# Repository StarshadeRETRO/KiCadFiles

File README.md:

# KiCadFiles
This is a repository of KiCad files for various retro gaming systems and related accessories. Unless otherwise noted, all files in this repository are licensed under the BSD-3-Clause license.

When selling physical products based on the files within this repository, attribution via a text link within the product's listing that leads to this repository as well as a text-based notice indicating the URL of this project and what was used in any included documentation or manuals is considered sufficient for fulfilling the license. If you intend to sell the PCBs be sure to remove the Starshade logo first -- see the section on the logo below for more details. Attribution should not be made in a way that suggests affiliation, endorsement, etc.

## Symbols & Footprints
Symbols and footprints in this repository are used in our other projects. You can use them in your projects too!

## PCBs
This repository contains a mix of finished, working, and work-in-progress PCBs as well as PCBs that are not intended to be used as-is but rather as templates you can use to start a project with accurate dimensions that will fit into the OEM location.

## The Starshade Logo
The Starshade logo is used many times throughout this repository, however, it is ***not*** included as part of the project's open license. You *may **not*** use the logo outside of this repository without permission. You **must** remove the logo from products you produce for commercial purposes (i.e. resale, promotion, etc). The logo can be left as is when having PCBs produced for personal use (limit of 5 PCBs per type/revision).

Other than not being able to use Starshade logo there are no further restrictions on commercial use. After removing the logo there are no limits on use, production run size, etc. Removal of the logo is primarily to avoid confusion about who produced/provided the PCB.

## Donations
All donations made to the project go towards furthering this and other projects. They are used to purchase equipment, components, etc. If you want your donation to go towards something specific, you can contact us before making it so we can ensure that it happens. We can provide proof that your donation went towards your desired goal if it is possible/practical.

## Store
Profit from purchases made from the [StarshadeRETRO store](https://store.starshade.dev/) goes towards furthering the development of various projects, including this one, the same as donations do. The only difference is you get something in return when you buy from the store. This is generally preferred over a direct contribution so that you get something in return.

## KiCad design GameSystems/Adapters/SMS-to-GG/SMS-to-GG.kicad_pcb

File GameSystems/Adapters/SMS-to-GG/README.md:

# SMS-to-GG Adapter
Converts a Master System slot to Game Gear for dumping cartridges. Intended for use with the [OSCR HW5](https://github.com/sanni/cartreader).

If getting this made, use a 1.6mm or 1.4mm PCB thickness. 1.6mm is a little tight but is recommended. It keeps the adapter more stable when inserting and removing GG cartridges. 1.4mm will fit a little easier but will wobble a bit when inserting and removing cartridges. While most SMS games seem to be 1.55mm, some SMS games are 1.7mm, so while 1.6mm is a bit tight it's not unrealistic for the system.

You can purchase this adapter [from our store](https://store.starshade.dev/en-gb/product/oscr-and-accessories/oscr-accessories/oscr-adapter-game-gear).

## Revision History
| Rev | Description                                                                                   | Status          |
| --- | --------------------------------------------------------------------------------------------- | --------------- |
| 1   | Initial                                                                                       | ❌ Broken       |
| 2   | Fixed misaligned mounting holes.                                                              | ❌ Incompatible |
| 3   | Moved slot footprint up to allow room for RetroSix GameSlot GG PCB and added a header for it. | ✔️ Verified     |
| 4   | Updated silkscreen and disclaimer formatting and wording. No mechanical difference vs Rev 3.  | ✔️ Verified     |

*SEGA and Game Gear are registered trademarks of SEGA CORPORATION (Japan). SEGA Master System is a trademark of Sega of America, Inc./SEGA CORPORATION (Japan). Neither affiliated with, nor authorized, sponsored, or approved by SEGA.*
*RetroSix is a registered trademark of Luke Malpass (UK). Neither affiliated with, nor authorized, sponsored, or approved by RetroSix/Luke Malpass.*

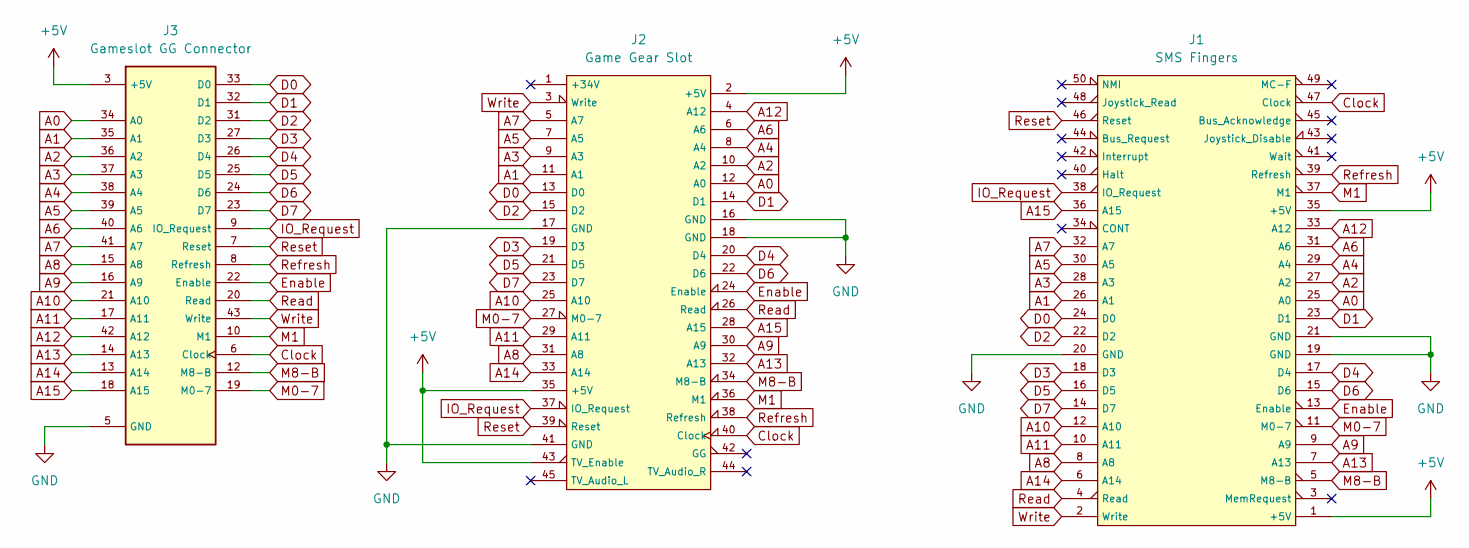
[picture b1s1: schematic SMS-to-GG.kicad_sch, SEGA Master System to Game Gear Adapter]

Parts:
J1: SMS Fingers; SG_SMS_CARTRIDGE_FINGERS
J2: Game Gear Slot; SG_GG_CARTRIDGE_SLOT_2H
J3: Gameslot GG Connector; FPC Connector - 45-pin - Multiple; LCSC C2998867

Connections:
+5V: J1.1 (+5V), J1.35 (+5V), J2.2 (+5V), J2.35 (+5V), J2.43 (TV_Enable), J3.3 (+5V), J3.11 (+5V), J3.44 (+5V)
A0: J1.25 (A0), J2.12 (A0), J3.34 (A0)
A1: J1.26 (A1), J2.11 (A1), J3.35 (A1)
A2: J1.27 (A2), J2.10 (A2), J3.36 (A2)
A3: J1.28 (A3), J2.9 (A3), J3.37 (A3)
A4: J1.29 (A4), J2.8 (A4), J3.38 (A4)
A5: J1.30 (A5), J2.7 (A5), J3.39 (A5)
A6: J1.31 (A6), J2.6 (A6), J3.40 (A6)
A7: J1.32 (A7), J2.5 (A7), J3.41 (A7)
A8: J1.8 (A8), J2.31 (A8), J3.15 (A8)
A9: J1.9 (A9), J2.30 (A9), J3.16 (A9)
A10: J1.12 (A10), J2.25 (A10), J3.21 (A10)
A11: J1.10 (A11), J2.29 (A11), J3.17 (A11)
A12: J1.33 (A12), J2.4 (A12), J3.42 (A12)
A13: J1.7 (A13), J2.32 (A13), J3.14 (A13)
A14: J1.6 (A14), J2.33 (A14), J3.13 (A14)
A15: J1.36 (A15), J2.28 (A15), J3.18 (A15)
Clock: J1.47 (Clock), J2.40 (Clock), J3.6 (Clock)
D0: J1.24 (D0), J2.13 (D0), J3.33 (D0)
D1: J1.23 (D1), J2.14 (D1), J3.32 (D1)
D2: J1.22 (D2), J2.15 (D2), J3.31 (D2)
D3: J1.18 (D3), J2.19 (D3), J3.27 (D3)
D4: J1.17 (D4), J2.20 (D4), J3.26 (D4)
D5: J1.16 (D5), J2.21 (D5), J3.25 (D5)
D6: J1.15 (D6), J2.22 (D6), J3.24 (D6)
D7: J1.14 (D7), J2.23 (D7), J3.23 (D7)
Enable: J1.13 (Enable), J2.24 (Enable), J3.22 (Enable)
GND: J1.19 (GND), J1.20 (GND), J1.21 (GND), J2.16 (GND), J2.17 (GND), J2.18 (GND), J2.41 (GND), J3.5 (GND), J3.28 (GND), J3.29 (GND), J3.30 (GND), J3.S1 (SHIELD), J3.S2 (SHIELD)
IO_Request: J1.38 (IO_Request), J2.37 (IO_Request), J3.9 (IO_Request)
M0-7: J1.11 (M0-7), J2.27 (M0-7), J3.19 (M0-7)
M1: J1.37 (M1), J2.36 (M1), J3.10 (M1)
M8-B: J1.5 (M8-B), J2.34 (M8-B), J3.12 (M8-B)
Read: J1.4 (Read), J2.26 (Read), J3.20 (Read)
Refresh: J1.39 (Refresh), J2.38 (Refresh), J3.8 (Refresh)
Reset: J1.46 (Reset), J2.39 (Reset), J3.7 (Reset)
Write: J1.2 (Write), J2.3 (Write), J3.43 (Write)

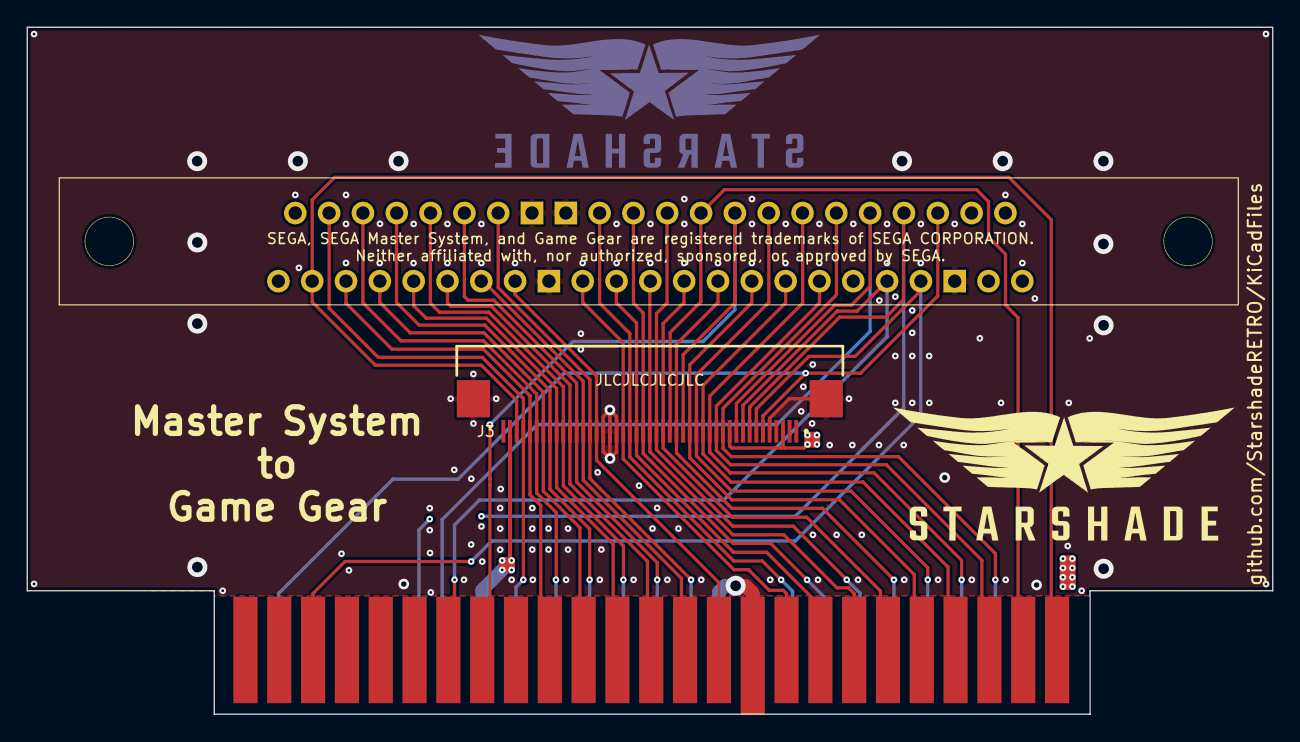
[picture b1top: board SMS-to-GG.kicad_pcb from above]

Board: 4 copper layers, 93.5 x 51.6 mm, 3 parts (0 on the bottom side), 36 nets.

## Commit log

2022-12-15 Add GG symbols, footprints, and sample cartridge PCB
    Untested.
2022-12-15 Reorganizing
    - Moved symbol and footprint libraries to a dedicated library folder.
    - Renamed symbol and foot print libraries to names based on the manufacturer of the targeted devices.
    - Clarified symbol, footprint, and library descriptions.
    - Updated and added READMEs.
    - Added images for symbols, footprints, and PCBs.
    - Added trademark disclaimers.
2022-12-16 Add SMS to libs + add Master System to Game Gear adapter
2022-12-16 Update library README
2023-04-01 Update SMS to GG adapter and GG slot.
    Was electrically correct but the NPTHs were slightly off.
2023-04-01 Update README files
2024-05-08 SMS-to-GG revisions + more
    * Updated the SMS-to-GG adapter from Rev 2 to Rev 4.
    * Rev 3 (not in repository):
    * Moved GG slot footprint up to allow room for the RetroSix GG slot connector PCB.
    * Added RetroSix GG slot FPC header directly to PCB.
    * Rev 4:
    * Fixed silkscreen disclaimers to refer to SEGA (Japan).

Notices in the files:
GameSystems/Adapters/SMS-to-GG/SMS-to-GG.kicad_pcb:
©2022-2024 StarshadeRETRO; License: BSD-3-Clause
parts and their libraries:
Copyright: ©2022-2024 StarshadeRETRO
License: BSD-3-Clause
©2020-2024 Remy Starshade. All rights reserved. Use on commercial products is prohibited.
